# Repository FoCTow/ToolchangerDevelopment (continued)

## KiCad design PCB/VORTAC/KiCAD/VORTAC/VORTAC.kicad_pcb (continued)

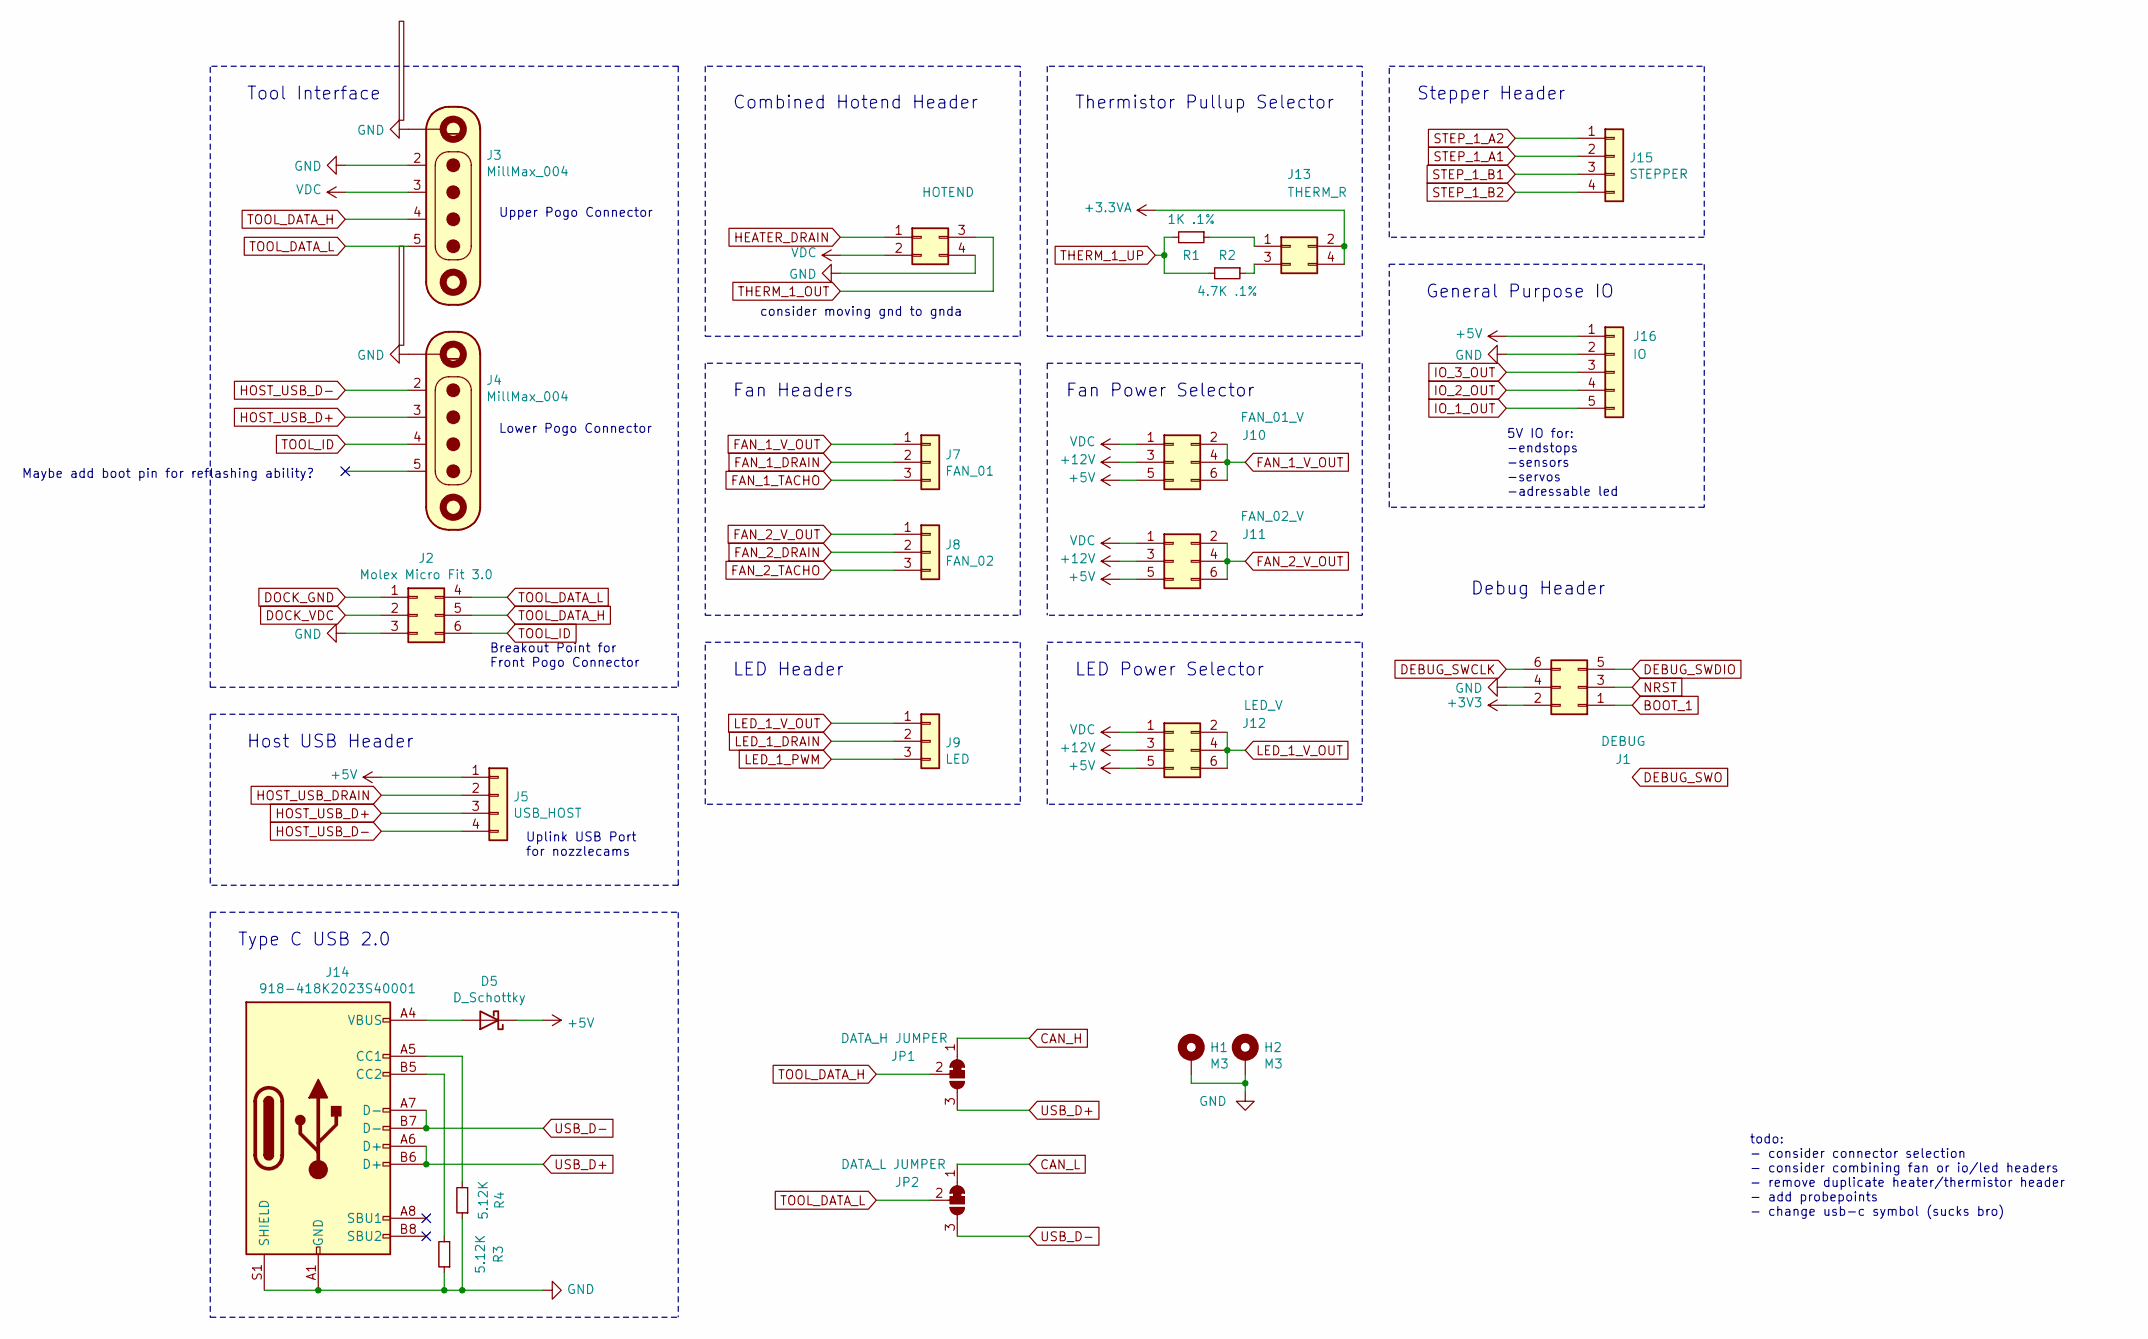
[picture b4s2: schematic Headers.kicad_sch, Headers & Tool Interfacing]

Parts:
D5: D_Schottky; D_SOD-123; LCSC C37049
H1, H2: M3; MountingHole_3mm_Pad_Via
J1: DEBUG; PinHeader_2x03_P1.27mm_Vertical
J2: Molex Micro Fit 3.0; Molex_Micro-Fit_3.0_43045-0612_2x03_P3.00mm_Vertical
J3, J4: MillMax_004; MillMax-858-10-004-10-012000; Mouser 575-8582200480012101
J5: USB_HOST; JST_PH_B4B-PH-K_1x04_P2.00mm_Vertical; LCSC C144395
J6: HOTEND; Molex_Micro-Fit_3.0_43045-0412_2x02_P3.00mm_Vertical
J7: FAN_01; JST_PH_B3B-PH-K_1x03_P2.00mm_Vertical; LCSC C144394
J8: FAN_02; JST_PH_B3B-PH-K_1x03_P2.00mm_Vertical; LCSC C144394
J9: LED; JST_PH_B3B-PH-K_1x03_P2.00mm_Vertical; LCSC C158012
J10: FAN_01_V; PinHeader_2x03_P1.27mm_Vertical
J11: FAN_02_V; PinHeader_2x03_P1.27mm_Vertical
J12: LED_V; PinHeader_2x03_P1.27mm_Vertical
J13: THERM_R; PinHeader_2x02_P1.27mm_Vertical
J14: 918-418K2023S40001; USB_C_Receptacle_XKB_U262-16XN-4BVC11; LCSC C167321
J15: STEPPER; JST_PH_S4B-PH-K_1x04_P2.00mm_Horizontal; LCSC C144395
J16: IO; JST_PH_B5B-PH-K_1x05_P2.00mm_Vertical; LCSC C157991
JP1: DATA_H JUMPER; SolderJumper-3_P1.3mm_Bridged12_Pad1.0x1.5mm
JP2: DATA_L JUMPER; SolderJumper-3_P1.3mm_Bridged12_Pad1.0x1.5mm
R1: 1K .1%; R_0402_1005Metric
R2: 4.7K .1%; R_0402_1005Metric
R3, R4: 5.12K; R_0402_1005Metric

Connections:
+3.3VA: J13.2, J13.4; also elsewhere on the board
+3V3: J1.2; also elsewhere on the board
+5V: D5.1 (K), J5.1, J10.5, J11.5, J12.5, J16.1; also elsewhere on the board
+12V: J10.3, J11.3, J12.3; also elsewhere on the board
BOOT_1: J1.1; also elsewhere on the board
CAN_H: JP1.1 (A); also elsewhere on the board
CAN_L: JP2.1 (A); also elsewhere on the board
DEBUG_SWCLK: J1.6; also elsewhere on the board
DEBUG_SWDIO: J1.5; also elsewhere on the board
DOCK_GND: J2.1; also elsewhere on the board
DOCK_VDC: J2.2; also elsewhere on the board
FAN_1_DRAIN: J7.2; also elsewhere on the board
FAN_1_TACHO: J7.3; also elsewhere on the board
FAN_1_V_OUT: J7.1, J10.2, J10.4, J10.6
FAN_2_DRAIN: J8.2; also elsewhere on the board
FAN_2_TACHO: J8.3; also elsewhere on the board
FAN_2_V_OUT: J8.1, J11.2, J11.4, J11.6
GND: H1.1, H2.1, J1.4, J2.3, J3.1, J3.2, J4.1, J6.4, J14.A1 (GND), J14.A12 (GND), J14.B1 (GND), J14.B12 (GND), J14.S1 (SHIELD), J16.2, R3.1, R4.1; also elsewhere on the board
HEATER_DRAIN: J6.1; also elsewhere on the board
HOST_USB_D+: J4.3, J5.3
HOST_USB_D-: J4.2, J5.4
HOST_USB_DRAIN: J5.2; also elsewhere on the board
IO_1_OUT: J16.5; also elsewhere on the board
IO_2_OUT: J16.4; also elsewhere on the board
IO_3_OUT: J16.3; also elsewhere on the board
LED_1_DRAIN: J9.2; also elsewhere on the board
LED_1_PWM: J9.3; also elsewhere on the board
LED_1_V_OUT: J9.1, J12.2, J12.4, J12.6
NRST: J1.3; also elsewhere on the board
unnamed: D5.2 (A), J14.A4 (VBUS), J14.A9 (VBUS), J14.B4 (VBUS), J14.B9 (VBUS)
unnamed: J13.1, R1.1
unnamed: J13.3, R2.1
unnamed: J14.A5 (CC1), R4.2
unnamed: J14.B5 (CC2), R3.2
STEP_1_A1: J15.2; also elsewhere on the board
STEP_1_A2: J15.1; also elsewhere on the board
STEP_1_B1: J15.3; also elsewhere on the board
STEP_1_B2: J15.4; also elsewhere on the board
THERM_1_OUT: J6.3; also elsewhere on the board
THERM_1_PIN: R1.2, R2.2; also elsewhere on the board
TOOL_DATA_H: J2.5, J3.4, JP1.2 (C)
TOOL_DATA_L: J2.4, J3.5, JP2.2 (C)
TOOL_ID: J2.6, J4.4; also elsewhere on the board
USB_D+: J14.A6 (D+), J14.B6 (D+), JP1.3 (B); also elsewhere on the board
USB_D-: J14.A7 (D-), J14.B7 (D-), JP2.3 (B); also elsewhere on the board
VDC: J3.3, J6.2, J10.1, J11.1, J12.1; also elsewhere on the board

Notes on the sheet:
Maybe add boot pin for reflashing ability?
todo: - consider connector selection - consider combining fan or io/led headers - remove duplicate heater/thermistor header - add probepoints - change usb-c symbol (sucks bro)
General Purpose IO
Thermistor Pullup Selector
LED Header
Breakout Point for Front Pogo Connector
Tool Interface
Stepper Header
Combined Hotend Header
LED Power Selector
Host USB Header
Upper Pogo Connector
Uplink USB Port for nozzlecams
consider moving gnd to gnda
5V IO for: -endstops -sensors -servos -adressable led
Fan Power Selector
Lower Pogo Connector
Fan Headers
Debug Header
Type C USB 2.0

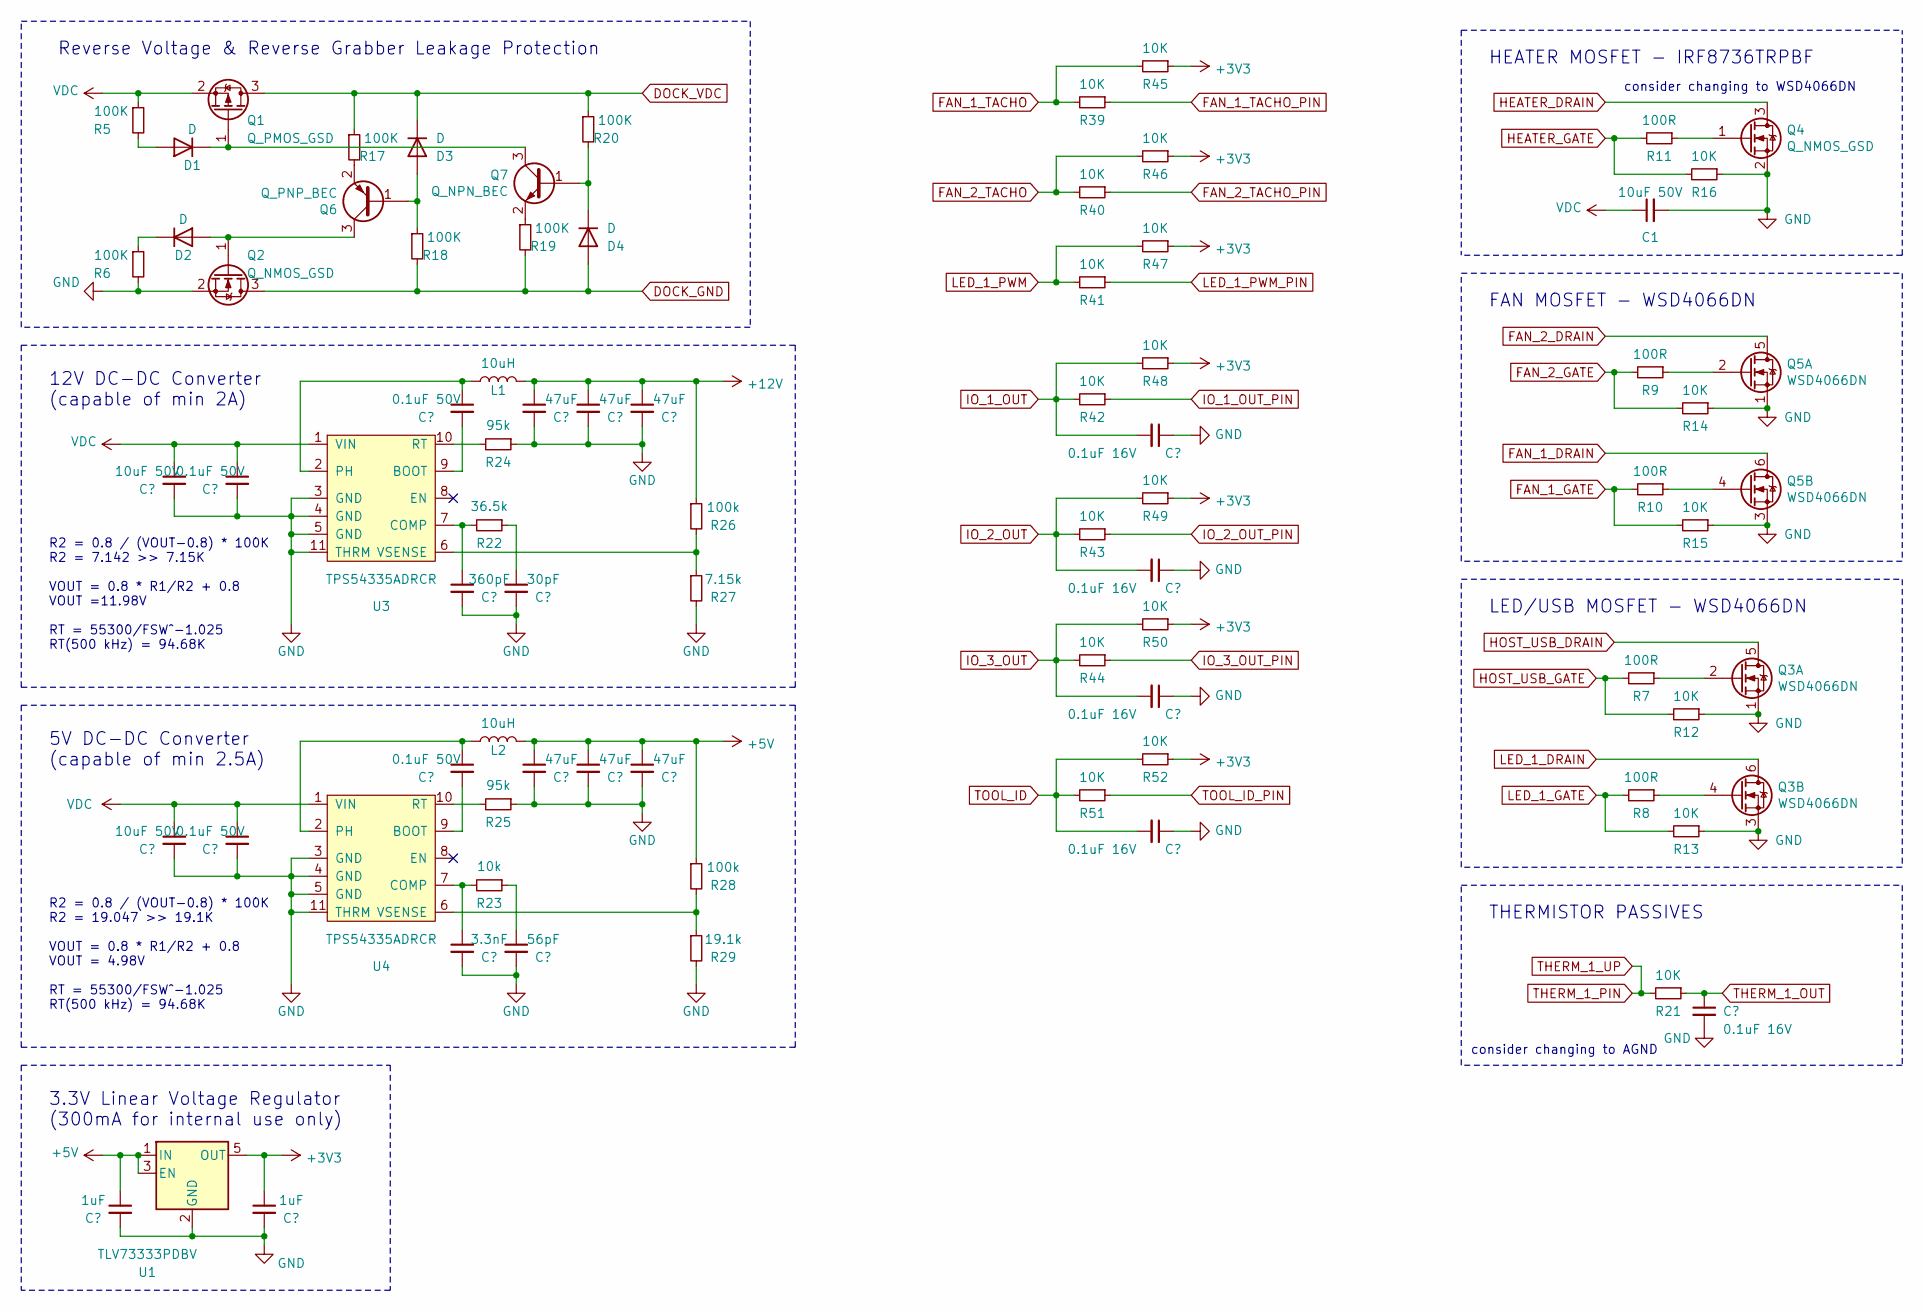
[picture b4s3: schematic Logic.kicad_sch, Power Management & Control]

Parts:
C1, C4, C5: 10uF 50V; C_1206_3216Metric; LCSC C89632
C2, C46, C47, C48, C49: 0.1uF 16V; C_0402_1005Metric; LCSC C1525
C3, C8: 1uF; C_0603_1608Metric
C6, C7, C9, C11: 0.1uF 50V; C_0603_1608Metric; LCSC C1591
C10: 360pF; C_0603_1608Metric; LCSC C458904
C12: 3.3nF; C_0603_1608Metric; LCSC C152910
C13: 30pF; C_0603_1608Metric; LCSC C123555
C14: 56pF; C_0603_1608Metric; LCSC C431816
C15, C17, C19: 47uF; C_1206_3216Metric; LCSC C403725
C16, C18, C20: 47uF; C_0805_2012Metric; LCSC C466799
D1, D2, D3, D4: D; D_SOD-923
L1, L2: 10uH; L_Sunlord_MWSA0518_5.4x5.2mm; LCSC C408412
Q1: Q_PMOS_GSD; IRF9310PbF-1_SO-8_ThermalPad; LCSC C92305
Q2, Q4: Q_NMOS_GSD; IRF9310PbF-1_SO-8_ThermalPad; LCSC C51630
Q3, Q5: WSD4066DN; WSD4066DN_ThermalPad; LCSC C377861
Q6: Q_PNP_BEC; SOT-23; LCSC C8542
Q7: Q_NPN_BEC; SOT-23; LCSC C2150
R5, R6, R17, R18, R19, R20: 100K; R_0402_1005Metric
R7, R8, R9, R10, R11: 100R; R_0402_1005Metric
R12, R13, R14, R15, R16, R21, R39, R40, R41, R42, R43, R44, R45, R46, R47, R48, R49, R50, R51, R52: 10K; R_0402_1005Metric
R22: 36.5k; R_0402_1005Metric
R23: 10k; R_0402_1005Metric
R24, R25: 95k; R_0402_1005Metric
R26, R28: 100k; R_0402_1005Metric
R27: 7.15k; R_0402_1005Metric
R29: 19.1k; R_0402_1005Metric
U1: TLV73333PDBV; SOT-23-5; LCSC C408972
U3, U4: TPS54335ADRCR; VSON-10-1EP_3x3mm_P0.5mm_EP1.65x2.4mm_ThermalVias; LCSC C473400

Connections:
+3V3: C8.1, R45.1, R46.1, R47.1, R48.1, R49.1, R50.1, R52.1, U1.5 (OUT); also elsewhere on the board
+5V: C3.1, C16.1, C18.1, C20.1, L2.2, R28.1, U1.1 (IN), U1.3 (EN); also elsewhere on the board
+12V: C15.1, C17.1, C19.1, L1.2, R26.1; also elsewhere on the board
DOCK_GND: D4.2 (A), Q2.3 (D), R18.2, R19.2; also elsewhere on the board
DOCK_VDC: D3.1 (K), Q1.3 (D), R17.1, R20.1; also elsewhere on the board
FAN_1_DRAIN: Q5.6 (D2); also elsewhere on the board
FAN_1_GATE: R10.2, R15.2; also elsewhere on the board
FAN_1_TACHO: R39.2, R45.2; also elsewhere on the board
FAN_1_TACHO_PIN: R39.1
FAN_2_DRAIN: Q5.5 (D2); also elsewhere on the board
FAN_2_GATE: R9.2, R14.2; also elsewhere on the board
FAN_2_TACHO: R40.2, R46.2; also elsewhere on the board
FAN_2_TACHO_PIN: R40.1
GND: C1.2, C2.2, C3.2, C4.2, C5.2, C6.2, C7.2, C8.2, C10.2, C12.2, C13.2, C14.2, C15.2, C16.2, C17.2, C18.2, C19.2, C20.2, C46.1, C47.1, C48.1, C49.1, Q2.2 (S), Q3.1 (S2), Q3.3 (S2), Q4.2 (S), Q5.1 (S2), Q5.3 (S2), R6.2, R12.1, R13.1, R14.1, R15.1, R16.1, R24.1, R25.1, R27.2, R29.2, U1.2 (GND), U3.3 (GND), U3.4 (GND), U3.5 (GND), U3.11 (THRM), U4.3 (GND), U4.4 (GND), U4.5 (GND), U4.11 (THRM); also elsewhere on the board
HEATER_DRAIN: Q4.3 (D); also elsewhere on the board
HEATER_GATE: R11.2, R16.2; also elsewhere on the board
HOST_USB_DRAIN: Q3.5 (D2); also elsewhere on the board
HOST_USB_GATE: R7.2, R12.2; also elsewhere on the board
IO_1_OUT: C46.2, R42.2, R48.2; also elsewhere on the board
IO_1_OUT_PIN: R42.1; also elsewhere on the board
IO_2_OUT: C47.2, R43.2, R49.2; also elsewhere on the board
IO_2_OUT_PIN: R43.1; also elsewhere on the board
IO_3_OUT: C48.2, R44.2, R50.2; also elsewhere on the board
IO_3_OUT_PIN: R44.1; also elsewhere on the board
LED_1_DRAIN: Q3.6 (D2); also elsewhere on the board
LED_1_GATE: R8.2, R13.2; also elsewhere on the board
LED_1_PWM: R41.2, R47.2; also elsewhere on the board
LED_1_PWM_PIN: R41.1
unnamed: C9.1, L1.1, U3.2 (PH)
unnamed: C9.2, U3.9 (BOOT)
unnamed: C10.1, R22.2, U3.7 (COMP)
unnamed: C11.1, L2.1, U4.2 (PH)
unnamed: C11.2, U4.9 (BOOT)
unnamed: C12.1, R23.2, U4.7 (COMP)
unnamed: C13.1, R22.1
unnamed: C14.1, R23.1
unnamed: D1.1 (K), Q1.1 (G), Q7.3 (C)
unnamed: D1.2 (A), R5.2
unnamed: D2.1 (K), R6.1
unnamed: D2.2 (A), Q2.1 (G), Q6.3 (C)
unnamed: D3.2 (A), Q6.1 (B), R18.1
unnamed: D4.1 (K), Q7.1 (B), R20.2
unnamed: Q3.2 (G2), R7.1
unnamed: Q3.4 (G2), R8.1
unnamed: Q4.1 (G), R11.1
unnamed: Q5.2 (G2), R9.1
unnamed: Q5.4 (G2), R10.1
unnamed: Q6.2 (E), R17.2
unnamed: Q7.2 (E), R19.1
unnamed: R24.2, U3.10 (RT)
unnamed: R25.2, U4.10 (RT)
unnamed: R26.2, R27.1, U3.6 (VSENSE)
unnamed: R28.2, R29.1, U4.6 (VSENSE)
THERM_1_OUT: C2.1, R21.1; also elsewhere on the board
THERM_1_PIN: R21.2; also elsewhere on the board
TOOL_ID: C49.2, R51.2, R52.2; also elsewhere on the board
TOOL_ID_PIN: R51.1; also elsewhere on the board
VDC: C1.1, C4.1, C5.1, C6.1, C7.1, Q1.2 (S), R5.1, U3.1 (VIN), U4.1 (VIN); also elsewhere on the board

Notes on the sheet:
THERMISTOR PASSIVES
12V DC-DC Converter (capable of min 2A)
Reverse Voltage & Reverse Grabber Leakage Protection
R2 = 0.8 / (VOUT-0.8) * 100K R2 = 7.142 >> 7.15K VOUT = 0.8 * R1/R2 + 0.8 VOUT =11.98V RT = 55300/FSW^-1.025 RT(500 kHz) = 94.68K
R2 = 0.8 / (VOUT-0.8) * 100K R2 = 19.047 >> 19.1K VOUT = 0.8 * R1/R2 + 0.8 VOUT = 4.98V RT = 55300/FSW^-1.025 RT(500 kHz) = 94.68K
5V DC-DC Converter (capable of min 2.5A)
LED/USB MOSFET - WSD4066DN
3.3V Linear Voltage Regulator (300mA for internal use only)
consider changing to AGND
FAN MOSFET - WSD4066DN
consider changing to WSD4066DN
HEATER MOSFET - IRF8736TRPBF

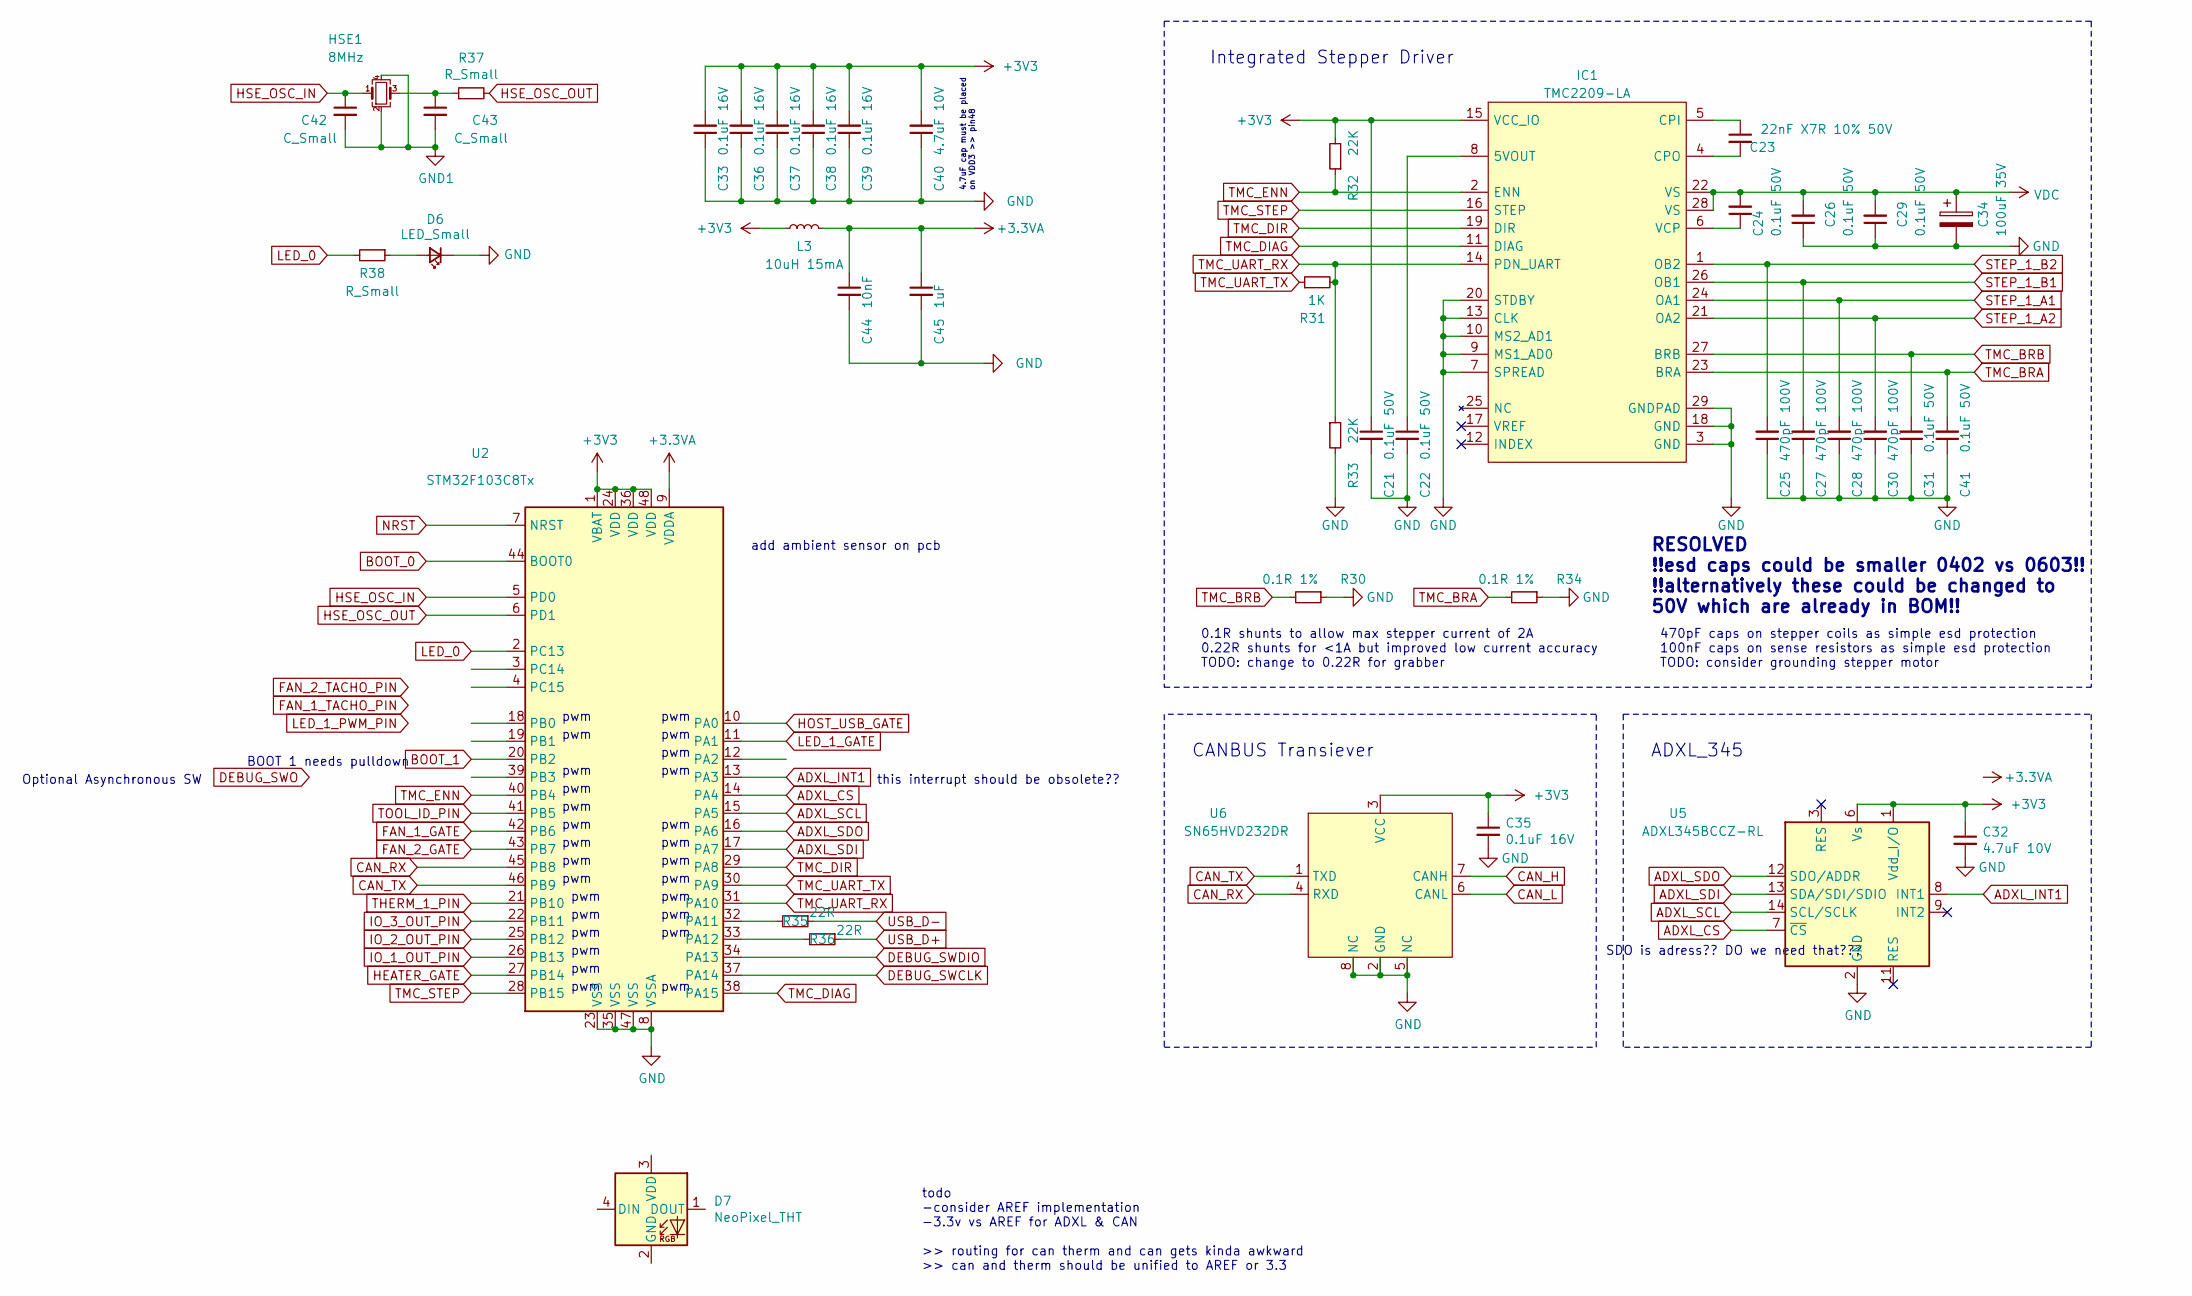
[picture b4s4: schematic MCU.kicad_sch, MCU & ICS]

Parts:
C21, C22, C24, C26, C29: 0.1uF 50V; C_0603_1608Metric; LCSC C1591
C23: 22nF X7R 10% 50V; C_0603_1608Metric
C25, C27, C28, C30: 470pF 100V; C_0603_1608Metric; LCSC C437459
C31, C41: 0.1uF 50V; C_0603_1608Metric; LCSC C66501
C32: 4.7uF 10V; C_0402_1005Metric
C33, C36, C37, C38, C39: 0.1uF 16V; C_0402_1005Metric; LCSC C1525
C34: 100uF 35V; CP_Elec_8x6.9
C35: 0.1uF 16V; C_0402_1005Metric
C40: 4.7uF 10V; C_0402_1005Metric; LCSC C368809
C42, C43: C_Small; C_0402_1005Metric
C44: 10nF; C_0402_1005Metric
C45: 1uF; C_0402_1005Metric
D6: LED_Small; LED_0402_1005Metric
D7: NeoPixel_THT; LED_Cree-PLCC4_2x2mm_CW
HSE1: 8MHz; Crystal_SMD_3225-4Pin_3.2x2.5mm; LCSC C518155
IC1: TMC2209-LA; tmc_2209_ThermalPad; LCSC C465949
L3: 10uH 15mA; L_0805_2012Metric; LCSC C76742
R30, R34: 0.1R 1%; R_1206_3216Metric; LCSC C346768
R31: 1K; R_0402_1005Metric
R32, R33: 22K; R_0402_1005Metric
R35, R36: 22R; R_0402_1005Metric
R37, R38: R_Small; R_0402_1005Metric
U2: STM32F103C8Tx; LQFP-48_7x7mm_P0.5mm; LCSC C8734
U5: ADXL345BCCZ-RL; LGA-14_3x5mm_P0.8mm_LayoutBorder1x6y; LCSC C579457
U6: SN65HVD232DR; SOIC-8_3.9x4.9mm_P1.27mm; LCSC C30530

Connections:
+3.3VA: C44.1, C45.1, L3.2, U2.9 (VDDA); also elsewhere on the board
+3V3: C21.1, C32.1, C33.2, C35.1, C36.2, C37.2, C38.2, C39.2, C40.2, IC1.15 (VCC_IO), L3.1, R32.2, U2.1 (VBAT), U2.24 (VDD), U2.36 (VDD), U2.48 (VDD), U5.1 (Vdd_I/O), U5.6 (Vs), U6.3 (VCC); also elsewhere on the board
ADXL_CS: U2.14 (PA4), U5.7 (~CS)
ADXL_INT1: U2.13 (PA3), U5.8 (INT1)
ADXL_SCL: U2.15 (PA5), U5.14 (SCL/SCLK)
ADXL_SDI: U2.17 (PA7), U5.13 (SDA/SDI/SDIO)
ADXL_SDO: U2.16 (PA6), U5.12 (SDO/ADDR)
BOOT_0: U2.44 (BOOT0)
BOOT_1: U2.20 (PB2); also elsewhere on the board
CAN_H: U6.7 (CANH); also elsewhere on the board
CAN_L: U6.6 (CANL); also elsewhere on the board
CAN_RX: U2.45 (PB8), U6.4 (RXD)
CAN_TX: U2.46 (PB9), U6.1 (TXD)
DEBUG_SWCLK: U2.37 (PA14); also elsewhere on the board
DEBUG_SWDIO: U2.34 (PA13); also elsewhere on the board
FAN_1_GATE: U2.42 (PB6); also elsewhere on the board
FAN_2_GATE: U2.43 (PB7); also elsewhere on the board
GND: C21.2, C22.2, C25.1, C26.1, C27.1, C28.1, C29.1, C30.1, C31.1, C32.2, C33.1, C34.2, C35.2, C36.1, C37.1, C38.1, C39.1, C40.1, C41.1, C44.2, C45.2, D6.1 (K), IC1.3 (GND), IC1.7 (SPREAD), IC1.9 (MS1_AD0), IC1.10 (MS2_AD1), IC1.13 (CLK), IC1.18 (GND), IC1.20 (STDBY), IC1.29 (GNDPAD), R30.1, R33.2, R34.1, U2.8 (VSSA), U2.23 (VSS), U2.35 (VSS), U2.47 (VSS), U5.2 (GND), U5.4 (GND), U5.5 (GND), U6.2 (GND), U6.5 (NC), U6.8 (NC); also elsewhere on the board
GND1: C42.2, C43.2, HSE1.2, HSE1.4
HEATER_GATE: U2.27 (PB14); also elsewhere on the board
HOST_USB_GATE: U2.10 (PA0); also elsewhere on the board
HSE_OSC_IN: C42.1, HSE1.1, U2.5 (PD0)
HSE_OSC_OUT: R37.2, U2.6 (PD1)
IO_1_OUT_PIN: U2.26 (PB13); also elsewhere on the board
IO_2_OUT_PIN: U2.25 (PB12); also elsewhere on the board
IO_3_OUT_PIN: U2.22 (PB11); also elsewhere on the board
LED_0: R38.2, U2.2 (PC13)
LED_1_GATE: U2.11 (PA1); also elsewhere on the board
NRST: U2.7 (NRST); also elsewhere on the board
unnamed: C22.1, IC1.8 (5VOUT)
unnamed: C23.1, IC1.5 (CPI)
unnamed: C23.2, IC1.4 (CPO)
unnamed: C24.1, IC1.6 (VCP)
unnamed: C43.1, HSE1.3, R37.1
unnamed: D6.2 (A), R38.1
unnamed: R35.2, U2.32 (PA11)
unnamed: R36.2, U2.33 (PA12)
STEP_1_A1: C28.2, IC1.24 (OA1); also elsewhere on the board
STEP_1_A2: C30.2, IC1.21 (OA2); also elsewhere on the board
STEP_1_B1: C27.2, IC1.26 (OB1); also elsewhere on the board
STEP_1_B2: C25.2, IC1.1 (OB2); also elsewhere on the board
THERM_1_PIN: U2.21 (PB10); also elsewhere on the board
TMC_BRA: C41.2, IC1.23 (BRA), R34.2
TMC_BRB: C31.2, IC1.27 (BRB), R30.2
TMC_DIAG: IC1.11 (DIAG), U2.38 (PA15)
TMC_DIR: IC1.19 (DIR), U2.29 (PA8)
TMC_ENN: IC1.2 (ENN), R32.1, U2.40 (PB4)
TMC_STEP: IC1.16 (STEP), U2.28 (PB15)
TMC_UART_RX: IC1.14 (PDN_UART), R31.2, R33.1, U2.31 (PA10)
TMC_UART_TX: R31.1, U2.30 (PA9)
TOOL_ID_PIN: U2.41 (PB5); also elsewhere on the board
USB_D+: R36.1; also elsewhere on the board
USB_D-: R35.1; also elsewhere on the board
VDC: C24.2, C26.2, C29.2, C34.1, IC1.22 (VS), IC1.28 (VS); also elsewhere on the board

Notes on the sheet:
pwm
RESOLVED !!esd caps could be smaller 0402 vs 0603!! !!alternatively these could be changed to 50V which are already in BOM!!
0.1R shunts to allow max stepper current of 2A 0.22R shunts for <1A but improved low current accuracy TODO: change to 0.22R for grabber
this interrupt should be obsolete??
ADXL_345
SDO is adress?? DO we need that???
Integrated Stepper Driver
4.7uF cap must be placed on VDD3 >> pin48
todo -consider AREF implementation -3.3v vs AREF for ADXL & CAN >> routing for can therm and can gets kinda awkward >> can and therm should be unified to AREF or 3.3
470pF caps on stepper coils as simple esd protection 100nF caps on sense resistors as simple esd protection TODO: consider grounding stepper motor
BOOT 1 needs pulldown
add ambient sensor on pcb
Optional Asynchronous SW
CANBUS Transiever

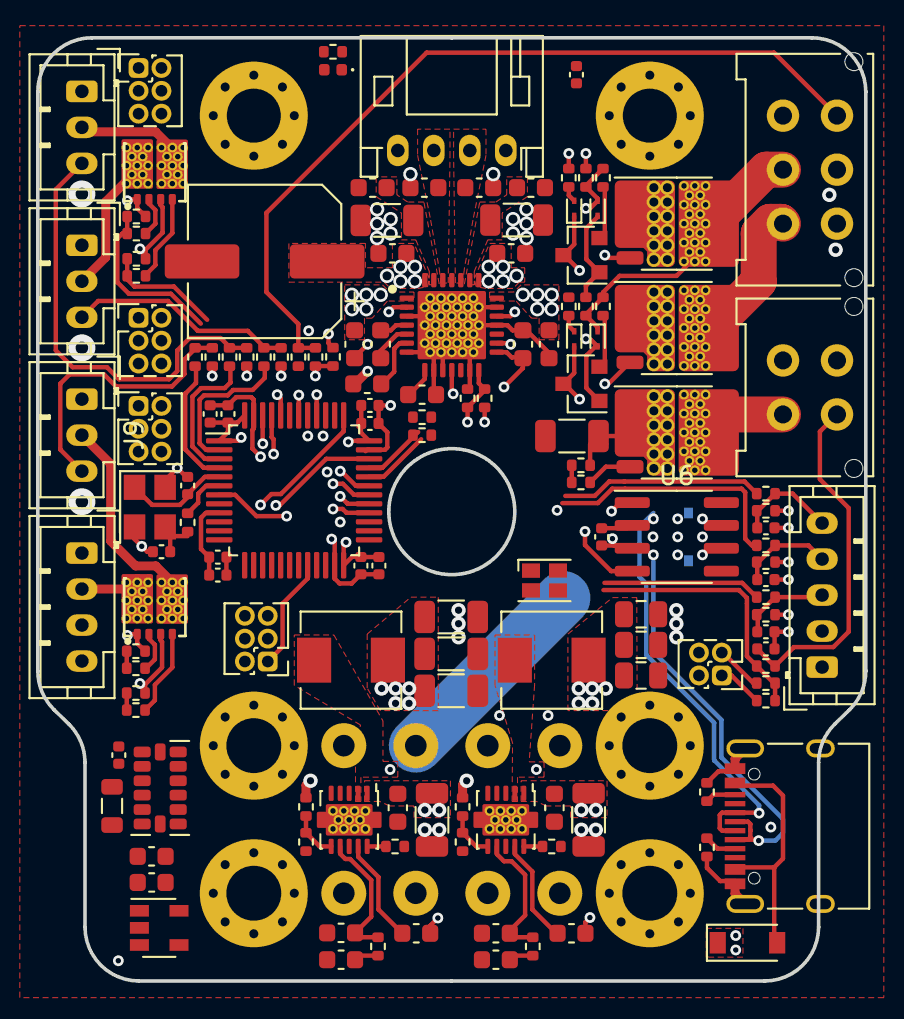
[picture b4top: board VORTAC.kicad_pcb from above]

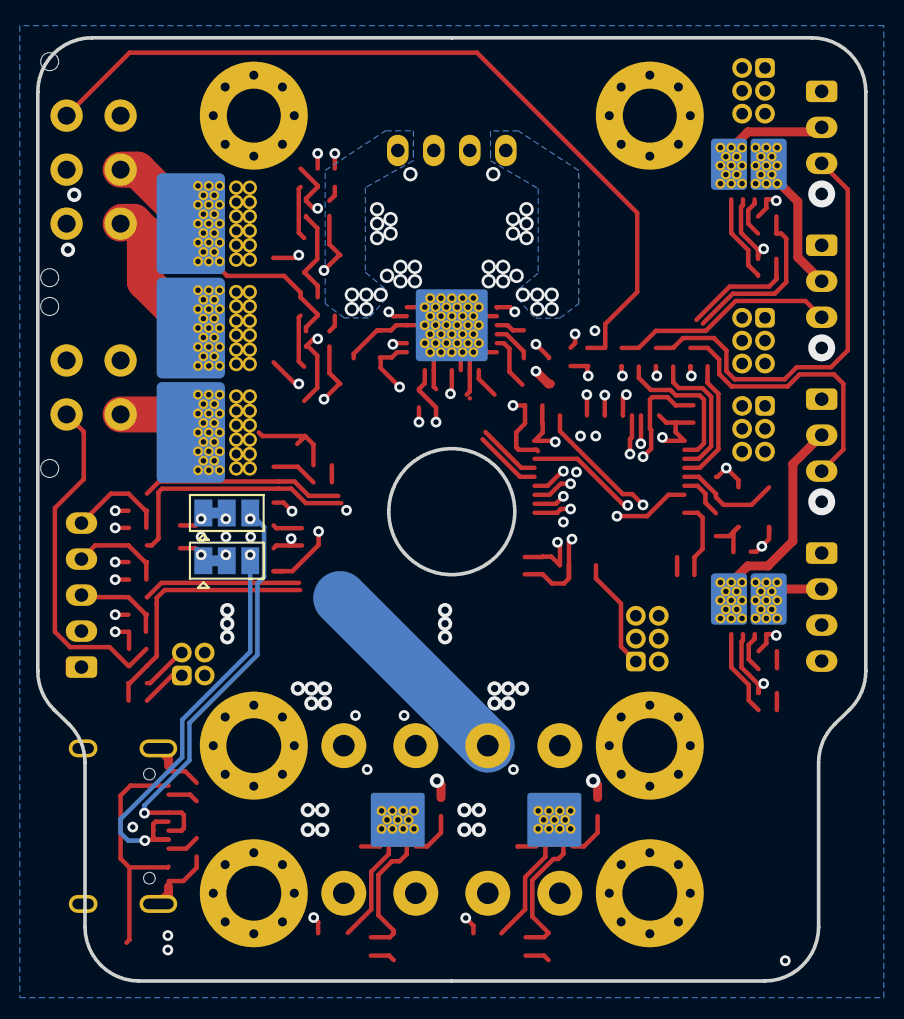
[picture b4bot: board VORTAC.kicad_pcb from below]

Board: 4 copper layers, 46.0 x 52.4 mm, 146 parts (4 on the bottom side), 107 nets.

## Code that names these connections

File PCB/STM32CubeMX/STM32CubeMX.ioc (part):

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Mcu.Name=STM32F103C(8-B)Tx
Mcu.Package=LQFP48
Mcu.UserName=STM32F103C8Tx
PA0-WKUP.GPIOParameters=GPIO_Label
PA0-WKUP.GPIO_Label=GPIO_OUT_TMC_ENN
PA0-WKUP.Signal=GPIO_Output
PA1.GPIOParameters=GPIO_Label
PA1.GPIO_Label=GPIO_OUT_TMC_DIR
PA1.Signal=GPIO_Output
PA11.Mode=Device
PA11.Signal=USB_DM
PA12.Mode=Device
PA12.Signal=USB_DP
PA13.Mode=Trace_Asynchronous_SW
PA13.Signal=SYS_JTMS-SWDIO
PA14.Mode=Trace_Asynchronous_SW
PA14.Signal=SYS_JTCK-SWCLK
PA2.Mode=Half_duplex(single_wire_mode)
PA2.Signal=USART2_TX
PA3.GPIOParameters=GPIO_Label
PA3.GPIO_Label=TIM2_CH4_TMC_STEP
PA3.Signal=S_TIM2_CH4
PA9.Mode=Half_duplex(single_wire_mode)
PA9.Signal=USART1_TX
PB0.GPIOParameters=GPIO_Label
PB0.GPIO_Label=GPIO_IN_TMC_DIAG
PB0.Signal=GPIO_Input
PB12.Mode=NSS_Signal_Hard_Output
PB12.Signal=SPI2_NSS
PB13.Mode=Full_Duplex_Master
PB13.Signal=SPI2_SCK
PB14.Mode=Full_Duplex_Master
PB14.Signal=SPI2_MISO
PB15.Mode=Full_Duplex_Master
PB15.Signal=SPI2_MOSI
PB3.Mode=Trace_Asynchronous_SW
PB3.Signal=SYS_JTDO-TRACESWO
PB8.Mode=CAN_Activate
PB8.Signal=CAN_RX
PB9.Mode=CAN_Activate
PB9.Signal=CAN_TX
PD0-OSC_IN.Mode=HSE-External-Oscillator
PD0-OSC_IN.Signal=RCC_OSC_IN
PD1-OSC_OUT.Mode=HSE-External-Oscillator
PD1-OSC_OUT.Signal=RCC_OSC_OUT
RCC.SYSCLKFreq_VALUE=72000000
RCC.SYSCLKSource=RCC_SYSCLKSOURCE_PLLCLK
board=custom

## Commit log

2021-09-11 INIT
2021-09-11 Added Step Files for Spring Loaded MillMax Connectors
2021-09-12 ToolChanger Lib and Pretty Content
2021-09-12 USB C
2021-09-12 updated StepFile Path
2021-09-12 Updated PCB Schematic
2021-09-22 pcb, step and headers
    -headers schematic updated
    -created rough pcb placement of headers
    -created step file for inspection in fusion 360
2021-09-22 footprints and libs
2021-09-22 Auto stash before merge of "main" and "origin/main"
2021-09-23 updated schematics
2021-09-23 TMC and Acc preperation
2021-10-02 add Gitignore
2021-10-02 GitIgnore and Footprints
2021-10-02 StepParts IRF
2021-10-02 Torex Stepdown Symbol
2021-10-03 Schematic and Lib Updates
2021-10-13 pushie
    updates and stuff
2021-10-17 progress
2021-10-23 Layouting & Footprints
    -Improved Thermal Footprint Conductivity
    -Improved Component Spacing
2021-10-24 IT l0oks like a Face FML =/
    thanks henny
2021-11-11 Routing WIP
2021-11-11 Reversed voltage selectors to simplify routing
2021-11-17 More Routing
2021-11-21 Still Routing
2021-11-21 Added Protective Passives
2021-11-21 Holiday Break <3
2021-12-10 Uppodateo des
2022-12-05 pushy
2024-08-16 Just fucking everything cause git doesnt sort shit
2024-08-16 Init Vortac_rev1
2025-04-14 added OPB666N
2025-04-26 hallo
2025-04-26 Added New EE_SX3350
2025-04-28 yipppieee
2025-04-28 added new usb
2025-04-28 more vbus
2025-04-29 Wayollaaaaa
2025-04-29 Fixed Library stuff
2025-04-29 changed Button Path
2025-04-29 added hvson 3_3
2025-04-29 pls merge Jenno
2025-04-29 Kanoolaaaa
2025-04-29 changed usb header
2025-04-29 Liebe Griasse zurrueck
2025-05-01 Gschenkle
2025-05-01 exported step
2025-05-04 Schematic updates
2025-05-04 Added LED-SMD
2025-05-04 Led Symbol Hand Wire footprint
2025-05-04 Schematic Updates - Changed the 5V Rail to a more space efficient implementation
2025-05-05 Schematic Updates Madrilla
2025-05-05 Update Symbol Librarys
2025-05-05 updated tmc library reference
2025-05-05 updated revs fabrication test
2025-05-05 added mosfet
2025-05-05 night night
2025-05-12 BOMBOM
2025-05-12 Anned Parts
2025-05-16 Evil Mita is v00:98
2025-05-18 No Body knows.... The trouble I've seen
2025-05-19 Nobody knows, my Sorrow...
2025-05-20 Girl Math
2025-05-21 footprints
2025-05-21 Route me like one of you French girls
2025-05-22 USB C Pain
2025-05-22 USB C Survivor
2025-05-23 On the Grind
2025-05-23 I NEED A HEEEROOO
2025-05-23 Tiny Tweaks
2025-05-23 Moved Panel Project and added Panel
2025-05-23 POanololel
2025-05-24 Tool can has pcb pls
2025-05-24 MEIN BEEEEEIIIINNNN
2025-05-25 Churro
2025-05-25 KONGSTRONG
2025-05-25 Panel Progress
2025-05-25 added missing R
2025-05-25 updated Outlines
2025-05-25 PCBCenterDXF
2025-05-25 Yippiieeeee
2025-05-25 Panel Center 1mm offset
2025-05-25 Vectors
2025-05-25 Logo Vector Panel Updates Logo Footprint Test
2025-05-25 updated Panel
2025-05-25 Render
